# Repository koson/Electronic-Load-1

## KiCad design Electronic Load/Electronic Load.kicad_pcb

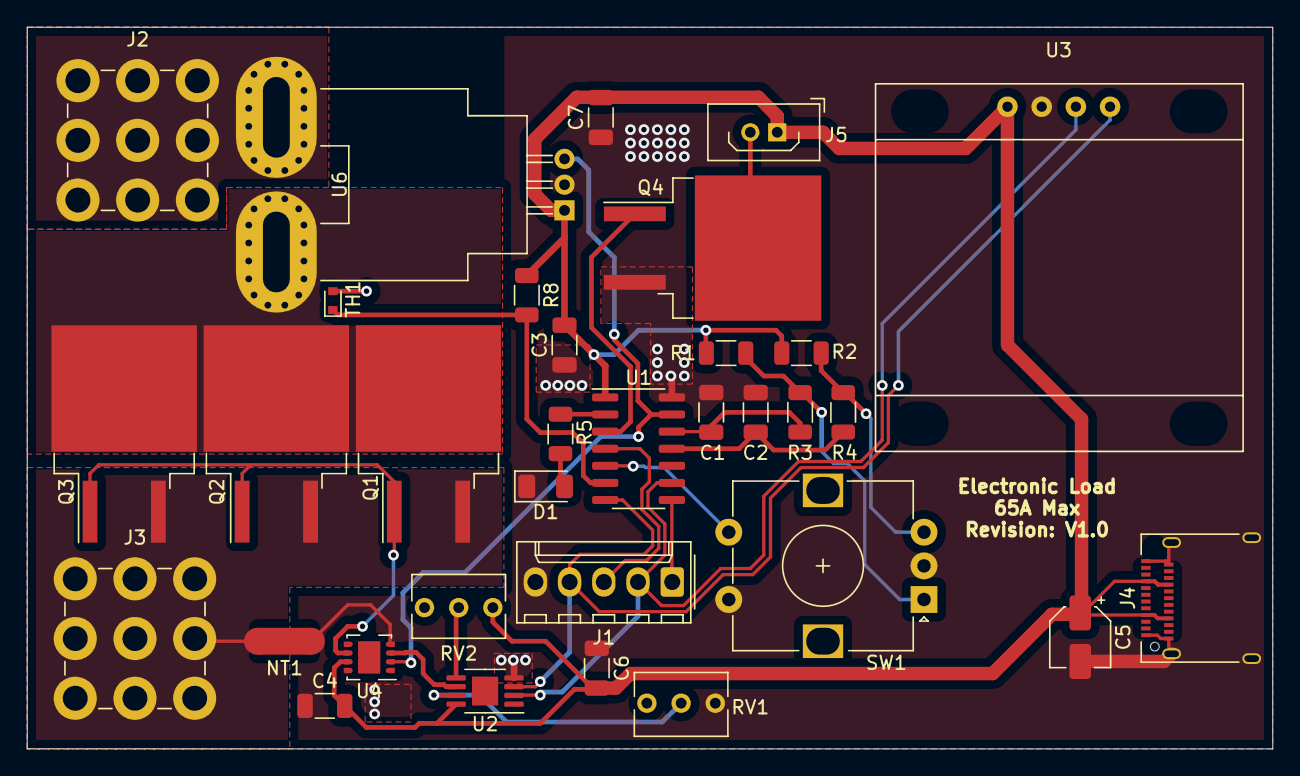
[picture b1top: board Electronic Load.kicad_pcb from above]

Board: 2 copper layers, 92.5 x 53.6 mm, 33 parts (0 on the bottom side), 24 nets.

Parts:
C1, C2: 0.01uF; C_1206_3216Metric
C3, C4, C6, C7: 1uF; C_1206_3216Metric
C5: 10uF; CP_Elec_4x5.4
D1: Red; LED_1206_3216Metric
J1: Programming Header; Molex_KK-254_AE-6410-05A_1x05_P2.54mm_Vertical
J2: Load_IN; Wuerth_REDCUBE-THR_WP-THRBU_74650195_THR
J3: Load_OUT; Wuerth_REDCUBE-THR_WP-THRBU_74650195_THR
J4: USB_C_Receptacle; USB_C_Receptacle_Amphenol_12401610E4-2A
J5: Fan Connector; Harwin_LTek-Male_02_P2.00mm_Vertical
NT1: Net-Tie_2; NetTie-2_SMD_Pad2.0mm
Q1, Q2, Q3, Q4: IRFS3306; TO-263-2
R1, R2, R3, R4, R8: 10k; R_1206_3216Metric
R5: 220; R_1206_3216Metric
RV1, RV2: R_POT; Potentiometer_Bourns_3266Y_Vertical
SW1: Rotary_Encoder_Switch; RotaryEncoder_Alps_EC12E-Switch_Vertical_H20mm
TH1: 10k; D_SOD-523
U1: ATtiny84-20SSU; SOIC-14_3.9x8.7mm_P1.27mm
U2: MCP4551; MSOP-8-1EP_3x3mm_P0.65mm_EP1.95x2.15mm
U3: SSD1306; SSD1306_OLED
U4: OPA277; Texas_S-PVSON-N8
U6: ACS758xCB-150U-PFF; Allegro_CB_PFF

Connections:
+5V: C3.2, C4.2, C5.1, C6.2, C7.2, J4.A4, J4.A9, J4.B4, J4.B9, J5.1, R1.1, R2.1, R8.1, RV2.3, U1.1, U2.8, U3.1, U4.7, U6.1
/A: R1.2, R3.2, SW1.A
/B: R2.2, R4.1, SW1.B
/Load_In: J2.1, U6.4
/MOSFET_Drain: Q1.2, Q2.2, Q3.2, U6.5
EncA: C1.1, R3.1, U1.12
EncB: C2.2, R4.2, U1.11
Enc_SW: SW1.S2, U1.5
Fan_Pin: Q4.1, U1.3
GND: C1.2, C2.1, C3.1, C4.1, C5.2, C6.1, C7.1, D1.1, J1.5, J4.A1, J4.A12, J4.B1, J4.B12, J4.S1, NT1.1, Q4.3, RV1.1, SW1.C, SW1.S1, TH1.2, U1.14, U2.4, U3.2, U4.4, U6.2
Gate: Q1.1, Q2.1, Q3.1, U4.6
MISO: J1.1, U1.8
unnamed: D1.2, R5.2
unnamed: J5.2, Q4.2
unnamed: R5.1, U1.2
unnamed: RV1.2, U2.7
unnamed: RV2.2, U2.5
unnamed: U2.6, U4.3
RESET: J1.3, U1.4
RETURN: J3.1, NT1.2, Q1.3, Q2.3, Q3.3
SCL: J1.2, U1.9, U2.2, U3.3
SDA_MOSI: J1.4, U1.7, U2.3, U3.4
Tout: R8.2, TH1.1, U1.6
Vout: U1.13, U4.2, U6.3

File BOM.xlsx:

Schematic Annotation | Part Number | Description | Qty | Price | Supplier | Total Cost | Link
U2 | MCP4551T-502E/MSCT-ND | Digital Potentiometer 5k Ohm 1 Circuit 257 Taps I²C Interface 8-MSOP | 1 | 0.95 | Digikey | 0.95 | https://www.digikey.com/en/products/detail/microchip-technol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
U1 | ATTINY84-20SSU-ND | AVR series Microcontroller IC 8-Bit 20MHz 8KB (4K x 16) FLASH 14-SOIC | 1 | 2.31 | Digikey | 2.31 | https://www.digikey.com/en/products/detail/microchip-technol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
J3 | 23-0022292051-ND | Connector Header Through Hole 5 position 0.100" (2.54mm) | 1 | 1.43 | Digikey | 1.43 | https://www.digikey.com/en/products/detail/molex/0022292051/1130591
J3 Mate | 23-0010112053-ND | 5 Rectangular Connectors - Housings Receptacle White 0.100" (2.54mm) | 1 | 0.28999999999999998 | Digikey | 0.28999999999999998 | https://www.digikey.com/en/products/detail/molex/0010112053/171981
J3 Crimps | WM3724CT-ND | Socket Contact Tin 22-28 AWG Crimp - | 5 | 0.12 | Digikey | 0.6 | https://www.digikey.com/en/products/detail/molex/0008700056/2421861
J1,J4 | 732-10888-1-ND | Pin Screw Terminal, Power Tap M5 Through Hole | 2 | 4.59 | Digikey | 9.18 | https://www.digikey.com/en/products/detail/w%C3%BCrth-elektr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
P1 | 12401610E4#2ACT-ND | USB-C (USB TYPE-C) USB 3.2 Gen 2 (USB 3.1 Gen 2, Superspeed + (USB 3.1)) Recept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 | 1 | 1.75 | Digikey | 1.75 | https://www.digikey.com/en/products/detail/amphenol-icc-comm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
U5 | 620-1355-ND | Current Sensor 150A 1 Channel Hall Effect, Open Loop Unidirectional 5-CB Formed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 | 1 | 9.6999999999999993 | Digikey | 9.6999999999999993 | https://www.digikey.com/en/products/detail/allegro-microsyst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
U3 | FZ1113-DIY | DIYmall 0.96" 0.96inch OLED LCD Display Module I2C IIC Serial 128x64 SSD1306 Dr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 | 1 | 9.99 | DIY Mall | 9.99 | http://www.diymalls.com/DIYmall-0.96-inch-IIC-OLED-Display-M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
SW1 | PEC12R-4220F-S0024-ND | Rotary Encoder Mechanical 24 Quadrature (Incremental) Vertical | 1 | 1.17 | Digikey | 1.17 | https://www.digikey.com/en/products/detail/bourns-inc/PEC12R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
C1,C2 | 732-12140-1-ND | 10000 pF ±10% 100V Ceramic Capacitor X7R 1206 (3216 Metric) | 2 | 0.11 | Digikey | 0.22 | https://www.digikey.com/en/products/detail/w%C3%BCrth-elektr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
U4 | 296-32187-1-ND | General Purpose Amplifier 1 Circuit - 8-VSON (4x4) | 1 | 3.92 | Digikey | 3.92 | https://www.digikey.com/en/products/detail/texas-instruments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
Heat Sink |  |  |  |  |  | 0
Q1-Q4 | IRFS3306TRLPBFCT-ND | N-Channel 60 V 120A (Tc) 230W (Tc) Surface Mount D2PAK | 4 | 2.58 | Digikey | 10.32 | https://www.infineon.com/dgdl/irfs3306pbf.pdf?fileId=5546d46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
TH1 | 296-TMP6131DYARCT-ND | PTC Thermistor 10 kOhms SC-79, SOD-523 | 1 | 0.32 | Digikey | 0.32 | https://www.digikey.com/en/products/detail/texas-instruments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
R1,R2,R3,R4, R8 | RNCS1206BKE10K0CT-ND | 10 kOhms ±0.1% 0.125W, 1/8W Chip Resistor 1206 (3216 Metric) Anti-Corrosive, Au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 | 5 | 0.54 | Digikey | 2.7 | https://www.digikey.com/en/products/detail/stackpole-electro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
R5 | P220ECT-ND | 220 Ohms ±5% 0.25W, 1/4W Chip Resistor 1206 (3216 Metric) Automotive AEC-Q200 T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 | 1 | 0.1 | Digikey | 0.1 | https://www.digikey.com/en/products/detail/panasonic-electro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
RV1 | 490-2881-ND | 20 kOhms 0.5W, 1/2W PC Pins Through Hole Trimmer Potentiometer Cermet 25.0 Turn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 | 1 | 1.5 | Digikey | 1.5 | https://www.digikey.com/en/products/detail/bourns-inc/PV36W2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
RV2 | 490-2888-ND | 5 kOhms 0.5W, 1/2W PC Pins Through Hole Trimmer Potentiometer Cermet 25.0 Turn 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 | 1 | 1.5 | Digikey | 1.5 | https://www.digikey.com/en/products/detail/bourns-inc/PV36W5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
D1 | 732-4992-1-ND | Red 630nm LED Indication - Discrete 1.9V 1206 (3216 Metric) | 1 | 0.21 | Digikey | 0.21 | https://www.digikey.com/en/products/detail/w%C3%BCrth-elektr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
J2 | 952-1769-ND | Connector Header Through Hole 2 position 0.079" (2.00mm) | 1 | 1.31 | Digikey | 1.31 | https://www.digikey.com/en/products/detail/harwin-inc/M80-85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
J2 Mate | 952-1189-ND | 2 Position Rectangular Receptacle Connector Crimp Gold 22 AWG | 1 | 1.82 | Digikey | 1.82 | https://www.digikey.com/en/products/detail/harwin-inc/M80-89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
C3 | 732-8430-1-ND | 10 µF 25 V Aluminum Electrolytic Capacitors Radial, Can - SMD - 2000 Hrs @ 105°C | 1 | 0.17 | Digikey | 0.17 | https://www.digikey.com/en/products/detail/w%C3%BCrth-elektr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
 |  |  |  |  | Total Cost | 61.460000000000008

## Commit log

2021-08-09 Added Resistive Divider Calculator
2021-08-09 Updated Resistor Calculator
2021-08-10 Added Controller Code
2021-08-11 Updated Schematics
2021-08-12 Updated Schematic
2021-08-13 Started PCB Layout
2021-08-13 Updated PCB
2021-08-14 Updated Simulations
2021-08-17 Updated PCB and code
2021-08-17 Updated Code
2021-08-19 Updated PCB
    Added potentiometers instead of fixed resistors on R6 and R7. Allows accurate changing of resistance to get good current ranges
2021-08-20 Reorganized Files
